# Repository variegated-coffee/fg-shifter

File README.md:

# FG Level Shifter

Fluid-o-tech FG20x/30x/40x gear pumps run at 5V, but Variegated Coffee boards prefer 3V3. The pumps also prefer a smooth control signal. PWM signals aren't. This is a really tiny board designed to fit into a Hammond 1551G project box allowing you to shift between 5V and 3V3, and to add an RC filter to smooth out the PWM signal.

*R2B is the current revision, but is yet to be manufactured. You shouldn't be the first to do so.*

## Features

* PCB outline matching a Hammond 1551G project box
* Terminal block for 24V power
* Connection to pump and to the controller can use either a terminal block, or something like a right-angled JST-XH connector
* 1206 and SOT-23-5 components for relatively easy hand soldering
* Extra holes for adding zip ties as strain relief

## Cabling

If you open up a FG series pump, you'll find the the stock cable is attached using a connector. That connector is a TE AMP CT 6 position connector (2.00 mm pitch). If you're unhappy with the stock cable, you should be able to create a new one.

## Changelog

* R1A -> R1B
  * Fixed hole positions
* R1B -> R2A 
  * Changed the board to not just be an RC filter, but to also do level shifting
* R2A -> R2B
  * Added bypass caps and Variegated coffee logo
  * Changed pinouts on connectors, to keep optional pins towards one edge

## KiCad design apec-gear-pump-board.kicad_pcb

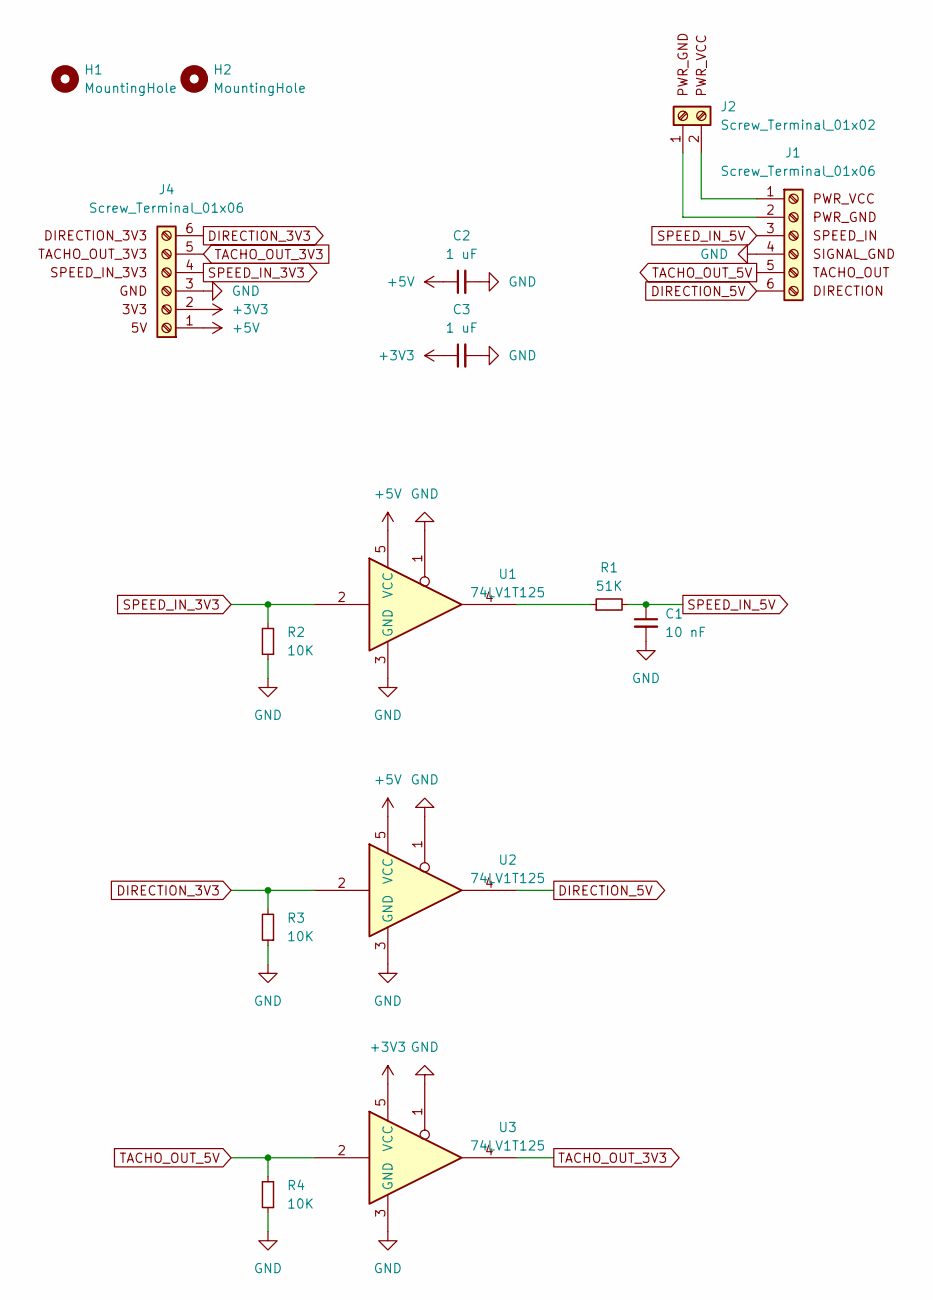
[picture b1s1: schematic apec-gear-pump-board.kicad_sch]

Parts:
C1: 10 nF; C_1206_3216Metric_Pad1.33x1.80mm_HandSolder; LCSC C1846
C2, C3: 1 uF; C_1206_3216Metric_Pad1.33x1.80mm_HandSolder; Digikey 1276-1068
H1, H2: MountingHole; MountingHole_2.5mm
J1, J4: Screw_Terminal_01x06; PinHeader_1x06_P2.54mm_Vertical
J2: Screw_Terminal_01x02; TerminalBlock_bornier-2_P5.08mm
R1: 51K; R_1206_3216Metric_Pad1.30x1.75mm_HandSolder; LCSC C17992
R2, R3, R4: 10K; R_1206_3216Metric_Pad1.30x1.75mm_HandSolder; LCSC C17902
U1, U2, U3: 74LV1T125; SOT-23-5_HandSoldering; LCSC C473338

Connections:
+3V3: C3.1, J4.2, U3.5 (VCC)
+5V: C2.1, J4.1, U1.5 (VCC), U2.5 (VCC)
DIRECTION_3V3: J4.6, R3.2, U2.2
DIRECTION_5V: J1.6 (DIRECTION), U2.4
GND: C1.2, C2.2, C3.2, J1.4 (SIGNAL_GND), J4.3, R2.1, R3.1, R4.1, U1.1, U1.3 (GND), U2.1, U2.3 (GND), U3.1, U3.3 (GND)
unnamed: J1.2 (PWR_GND), J2.1 (PWR_GND)
unnamed: J1.1 (PWR_VCC), J2.2 (PWR_VCC)
unnamed: R1.1, U1.4
SPEED_IN_3V3: J4.4, R2.2, U1.2
SPEED_IN_5V: C1.1, J1.3 (SPEED_IN), R1.2
TACHO_OUT_3V3: J4.5, U3.4
TACHO_OUT_5V: J1.5 (TACHO_OUT), R4.2, U3.2

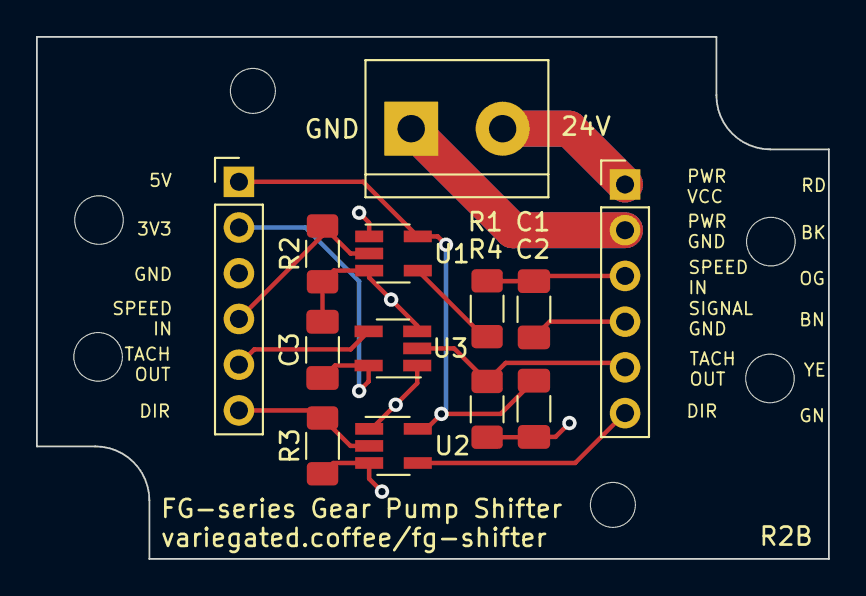
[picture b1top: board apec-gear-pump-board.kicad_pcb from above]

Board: 2 copper layers, 44.0 x 29.0 mm, 15 parts (0 on the bottom side), 12 nets.

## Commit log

2024-03-29 Initial import
2024-03-29 Fixed mistake
2024-03-30 Cleaned stuff up, and switched to wider tracks for Power
2024-03-31 Cleanup
2024-05-16 Updated the board to do level shifting
2024-06-01 Added decoupling caps and Variegated Coffee logo
2024-06-03 More silk screen on the back, changed pinout on the connectors, to put optional pins towards one edge
2024-11-02 Minor changes
